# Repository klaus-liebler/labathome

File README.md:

# lab@home

<a target="_blank" href="https://icons8.com/icon/cUjTrEUoGJ2Z/xing">Xing</a> icon by <a target="_blank" href="https://icons8.com">Icons8</a>
<a target="_blank" href="https://icons8.com/icon/3tC9EQumUAuq/github">GitHub</a> icon by <a target="_blank" href="https://icons8.com">Icons8</a>
<a target="_blank" href="https://icons8.com/icon/IuI5Yd3J3qcC/linkedin">LinkedIn</a> icon by <a target="_blank" href="https://icons8.com">Icons8</a>

## Was steckt dahinter?
Das Projekt "lab@home" entstand zu Beginn der Corona-Pandemie. Als Lehrer in einer Hochschule der angewandten Wissenschaften war es dem Initiator ein Anliegen, seinen Studierenden auch 
während des Lockdowns Zugang zu Laborexperimenten in den Bereichen Steuerungstechnik, Regelungstechnik und Informationstechnik zu geben. Leider konnten die Studierenden nicht
mehr in die Hochschullabors, also musste das Labor zu den Studierenden. Nur leider wäre ein Container voll Material pro Student etwas zu aufwändig. Etwas kleineres und vor allem
kostengünstigeres musste her. Und damit waren die grundsätzlichen Anforderungen umrissen und der Initiator machte mich ans Design...

## Was gehört zu lab@home und was kann man damit machen?
Lab@home besteht aus
- einem Hardware-Design
- einer Softwarekomponente
- dieser Dokumentation
- der Beschreibung von Laborexperimenten (nicht veröffentlicht, auf Anfrage stelle ich das gerne zur Verfügung)

Der Entwickler bezeichne lab@home als eine Lehr- und Lernplattform für den Einsatz in Bildungseinrichtungen in den Disziplinen Steuerungstechnik, Regelungstechnik und Informationstechnik.
Ein besonderer Fokus liegt dabei auf der Gebäudeautomation

## Was sind die einzigartigen Merkmale von lab@home?
Lab@home
- ist quelloffen und soll unter der MIT-Lizenz jedem Nutzen stiften!
- kann komplett über den Browser bedient werden   
- ist preiswert und unproblematisch nachbaubar
- kann vielfältig eingesetzt werden

## Genug des Blabla - bitte technisch konkret!
Die Hardware von lab@home ist auf einer 10x10cm großen Platine aufgebaut und enthält die folgenden Komponenten:
- Dual-Prozessor-Konzept
    - Applikation: ESP32-S3 (8M Flash, 2,5MB RAM, Wifi, Bluetooth)
    - I/O & Realtime: STM32G431 (128k Flash, 32k RAM)
- Speichererweiteung über microSD-Slot
- Kommunikation
  - Interne Busse: I2c & 1Wire
  - Extern: Wifi, Bluetooth, RS485 (z.B. für Modbus), CAN (z.B. für CANopen oder OBD2)
  - Optional durch Steckmodule: Ethernet (W5500), GSM (SIM7080G), LoRaWan (RFM95), 2,4GHz (NRF24L01)
- Benutzerinteraktion
  - Taster, Inkrementalencoder
  - IPS-Display 240x240 Pixel, 1,3Zoll (ST7789)
  - Vier RGB-LED (WS2812)
  - Lautsprecher, Mikrofon, Klinkenbuchsen für Aux-In, Line-Out, Kopfhörer (NAU88C22)
- Sensorik
  - Lufttemperatur, Temperatur des Heizwiderstandes (2x DS18B20)
  - Luftfeuchtigkeit (SHT20)
  - Umgebungshelligkeit (LDR)
  - Ausrichtungs und Beschleunigungssensor (LSM6DS3)
  - PIR-Bewegungsmelder
  - Drei universelle ADC-Eingänge, davon einer mit Spannungsteiler
  - Spannungs- und Strommessung
  - Eingänge für Hall-Encoder
  - Optional durch Steckmodule: CO2, Luftqualität, Distanzsensor, Farbsensor
- Aktorik
  - Heizwiderstand, Lüfter, weiße Power-LEDs (alle PWM-Ansteuerung)
  - Zwei universelle DAC-Ausgänge, davon einer mit 0-10V
  - Dreiphasiger Motortreiber (Brushless) (DRV8313)
  - Drei Schrittmotor-Treiber (TMC2209)
  - Anschlüsse für vier (optional sechs) Servos
- Stromversorgung
  - USB
  - USB PD oder PPS (max 20V, 5A, umgesetzt über das UCPD-Peripherial im STM32G431)
  - Hohlstecker 5,5mm
  - MC-Klemmen
  - 18650-Akku
  - Involviert in die Stromversorgung sind 
    - IP5306: Akkuladung, Boot-Converter auf 5V
    - TPS54202: Synchroner Abwärtswandler 8...24V -> 5V
    - TPS2116: Umschaltung zwischen Spannungsquellen
    - AMS1117: LDO 5V->3,3V

Die Software von lab@home besteht aus der eigentlichen Firmware und einer Webapplikation. Viele Experimente können über die Webapplikation gesteuert werden.
Nach dem ersten Start öffnet lab@home einen WIFI-Accesspoint, über den die Webapplikation erreichbar ist und labathome auch in ein bestehendes WIFI-Netzwerk eingebunden werden kann. Dank der Webapplikation benötigt der Anwender keine lokale Software und die Nutzung ist unabhängig vom Betriebssystem möglich (viele meiner Studierenden verwenden Apple-Rechner oder haben nur Chromebooks oder Android-Tablets). Die Webapplikation hat diese Features:
- Programmierung von lab@home mit Funktionsblöcken in Anlehnung an IEC61131 und VDI3814
  - darauf ist der Entwickler besonders stolz!!
  - Speichern und Laden von Programmen möglich
  - Es ist möglich, eine Startapplikation festzulegen, die lab@home automatisch beim Einschalten lädt und ausführt
  - Integrierter Debugger
  - Integrierter Simulator
  - Technisches Detail: Das Funktionsblock-Diagramm wird von einem Java-Script-Compiler im Browser zu einem Binärcode compiliert und "online" zum Mikrocontroller gesendet. Dieser bringt dann das Programm unmittelbar zur Ausführung
- Oberfläche für das Experiment "Identikation einer Regelstrecke mit dem Sprungantwort-Versuch"
- Oberfläche für das Experiment "Parametriertung eines PID-Reglers mit der Einstellregeln nach Chien, Hrones und Reswick"
- Konfigurationsoberfläche für Wifi
- Konfigurationsoberfläche für diverse Systemeinstellungen (in Arbeit)
- Online-Aktualisierung der kompletten Systemsoftware (in Arbeit)

# Getting Started - Hardware
Die aktuellen Schaltpläne und Layouts im KiCad-Format befinden sich im Verzeichnis labathome_pcb

# Getting Started - Software

Die Software muss individuell für jedes Board compiliert werden, weil während des von Gulp gesteuerten Gesamt-Build-Prozesses diverse individuelle Dateien erzeugt und eincompiliert werden. Dazu gehören:
- LabAtHome meldet sich per Sprachausgabe betriebsbereit. Die Ausgabe enthält auch den Hostnamen der Platine, der sich wiederum aus der MAC-Adresse ableitet. Alle Sprachausgaben werden zum Build-Zeitpunkt über Google TTS erzeugt und in Form von MP3-Dateien im Flash abgelegt. Ach ja, LabAtHome kann natürlich MP3 wiedergeben!
- LabAtHome kommuniziert natürlich verschlüsselt! Dazu wird ein privater Schlüssel und ein Zertifikat für eben den Hostnamen erzeugt

## Voraussetzungen
- Installiere Visual Studio Code
    - Installiere und konfiguriere die ESP-IDF Extension
    - Optional: Isntalliere die Extension "Serial Monitor"
- Installiere Node.js
- Installiere Python
- Installiere den Flatbuffers-Compiler (aka. runterladen https://github.com/google/flatbuffers/releases und ausführbare Datei in den "PATH" aufnehmen)
- Checke diverse Repositories aus (Ich gehe davon aus, dass alle Checkouts in c:/repos erfolgen. Einige Pfade sind in den Konfigurationsdateien absolut und auf diesen Pfad angepasst)
    - https://github.com/klaus-liebler/labathome
    - https://github.com/klaus-liebler/espidf-components
    - https://github.com/klaus-liebler/npm-packages
    - https://github.com/klaus-liebler/espidf-component-webmanager,
    - https://github.com/klaus-liebler/esp-idf-components-lcd
- Rufe npm i in den folgenden Verzeichnissen auf:
    - .../labathome/builder
    - .../npm-package/<diverse...>
- Editiere die Datei .../labathome/builder/gulpfile.ts im oberen Bereich direkt nach den Exports. Die Kommentare dort helfen hoffentlich beim Verständnis.
- Lab@Home nutzt die Google TTS Engine während des Build-Prozesses, um individuelle Sprachausgaben zu erzeugen. Der Computer, auf dem der Build durchgeführt wird, muss für den zugriff auf die Google Cloud TTS freigegeben sein: https://cloud.google.com/nodejs/docs/reference/text-to-speech/latest
- Öffne in VS Code eine ESP IDF Console und wechsele in das Verzeichnis .../labathome/builder
- Rufe npm run doOnce auf. Dies erzeugt u.a. ein selbst signiertes Zertifikat , das auf allen Computern als Stammzertifikat installiert werden kann und später zum Signieren der Board-Zertifikate verwendet wird.
- Rufe "npm update" in C:\repos\labathome\espidf-component-labathome\espidf-component-webmanager, auf
- Rufe "npm update" in "C:\repos\labathome\espidf-component-labathome\builder" auf
- Rume "npm run gulp" in "C:\repos\labathome\espidf-component-labathome\builder" auf. Dieses erstellt individuelle Board-Files und die gesamte Web-Anwendung
- TBC

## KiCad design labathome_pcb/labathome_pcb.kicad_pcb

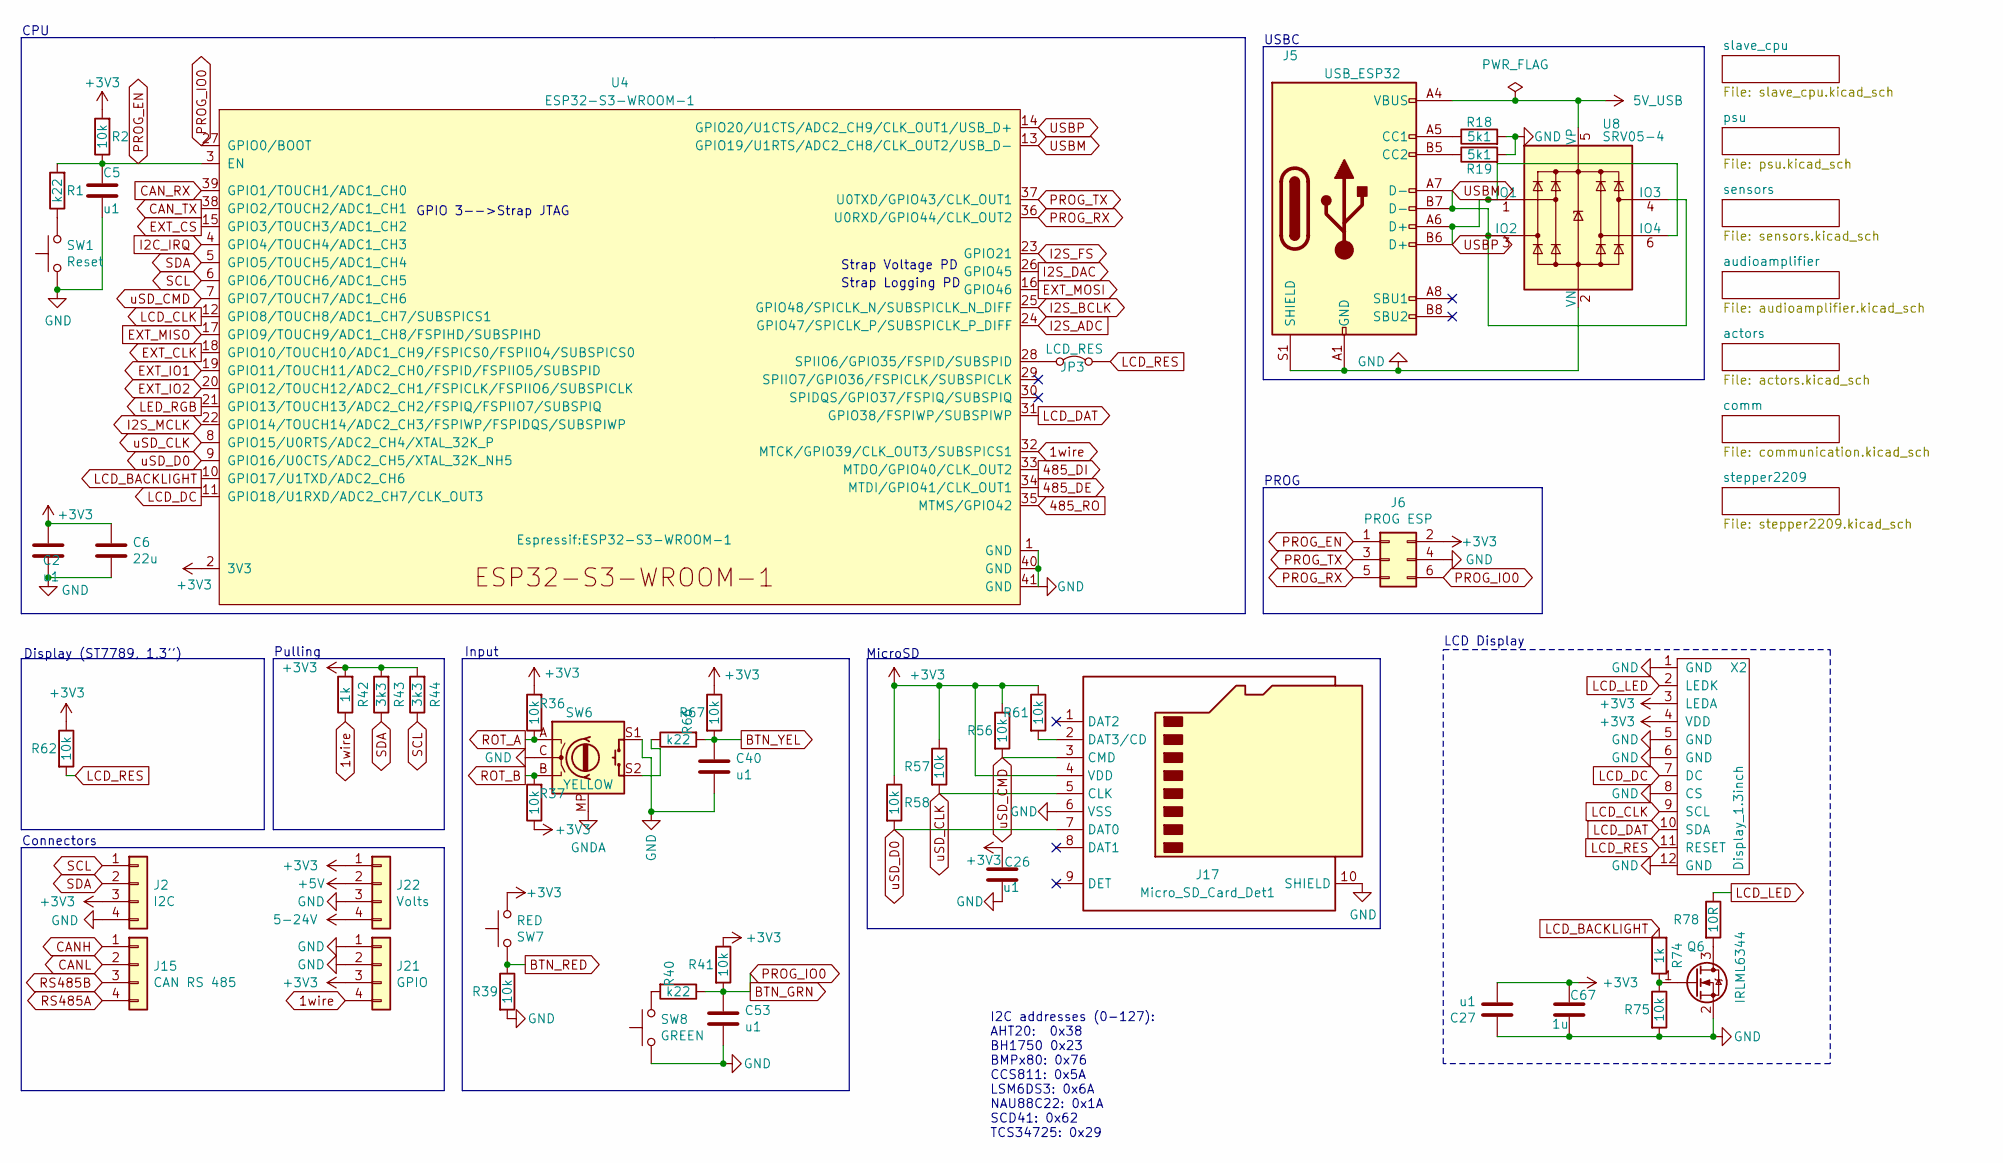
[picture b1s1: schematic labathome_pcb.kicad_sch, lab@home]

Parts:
C2, C5, C26, C27, C40, C53: u1; C_0201_0603Metric; MPN GRM033R61A104KE15D
C6: 22u; C_0603_1608Metric; MPN CL10A226MP8NUNE
C67: 1u; C_0402_1005Metric; MPN CL05A105KA5NQNC
J2: I2C; PhoenixContact_MC_1,5_4-G-3.5_1x04_P3.50mm_Horizontal_small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; MPN KF2EDGR-3.5-4P
J5: USB_ESP32; USB_C_Receptacle_HRO_TYPE-C-31-M-12_smaller; MPN TYPE-C-31-M-12
J6: PROG ESP; IDC_2x03_P1.27mm_Vertical
J15: CAN RS 485; PhoenixContact_MC_1,5_4-G-3.5_1x04_P3.50mm_Horizontal_small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; MPN KF2EDGR-3.5-4P
J17: Micro_SD_Card_Det1; microSD push; MPN TF PUSH
J21: GPIO; PhoenixContact_MC_1,5_4-G-3.5_1x04_P3.50mm_Horizontal_small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; MPN KF2EDGR-3.5-4P
J22: Volts; PhoenixContact_MC_1,5_4-G-3.5_1x04_P3.50mm_Horizontal_small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; MPN KF2EDGR-3.5-4P
JP3: LCD_RES; SolderJumper-2_P1.3mm_Bridged2Bar_RoundedPad1.0x1.5mm
Q6: IRLML6344; SOT-23; MPN AO3400
R1, R40, R66: k22; R_0402_1005Metric; MPN 0402WGF2200TCE
R2, R36, R37, R39, R41, R56, R57, R58, R61, R62, R67, R75: 10k; R_0201_0603Metric; MPN 0201WMF1002TEE
R18, R19: 5k1; R_0201_0603Metric; MPN RC0201FR-075K1L
R42, R74: 1k; R_0402_1005Metric; MPN 0402WGF1001TCE
R43, R44: 3k3; R_0402_1005Metric; MPN 0402WGF3301TCE
R78: 10R; R_1206_3216Metric; MPN 1206W4F100JT5E
SW1: Reset; Button_2x4x3,5_handsolder; MPN TS24CA 250gf 013
SW6: YELLOW; RotaryEncoder_EC11_SMD_handsolder; MPN EC11E0940501
SW7: RED; SW_Push_1P1T_NO_6x6mm_H6.5mm_Reverse; MPN TS-1095E-A6B3-D2
SW8: GREEN; SW_Push_1P1T_NO_6x6mm_H6.5mm_Reverse; MPN TS-1095E-A6B3-D2
U4: ESP32-S3-WROOM-1; MPN ESP32-S3-WROOM-1-N8R2
U8: SRV05-4; SOT-23-6; MPN SRV05-4
X2: Display_1.3inch; IPS_130

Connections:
1wire: J21.4, R42.1, U4.32 (MTCK/GPIO39/CLK_OUT3/SUBSPICS1); also elsewhere on the board
5-24V: J22.4; also elsewhere on the board
5V_USB: J5.A4 (VBUS), J5.A9 (VBUS), J5.B4 (VBUS), J5.B9 (VBUS), U8.5 (VP); also elsewhere on the board
485_DE: U4.34 (MTDI/GPIO41/CLK_OUT1); also elsewhere on the board
485_DI: U4.33 (MTDO/GPIO40/CLK_OUT2); also elsewhere on the board
485_RO: U4.35 (MTMS/GPIO42); also elsewhere on the board
+3V3: C2.1, C6.1, C26.2, C27.2, C67.1, J2.3, J6.2, J17.4 (VDD), J21.3, J22.1, R2.2, R36.2, R37.1, R41.1, R42.2, R43.2, R44.2, R56.1, R57.1, R58.1, R61.1, R62.1, R67.1, SW7.1, U4.2 (3V3), X2.3 (LEDA), X2.4 (VDD); also elsewhere on the board
+5V: J22.2; also elsewhere on the board
BTN_GRN: C53.2, J6.6, R40.1, R41.2, U4.27 (GPIO0/BOOT)
BTN_RED: R39.1, SW7.2; also elsewhere on the board
BTN_YEL: C40.2, R66.2, R67.2; also elsewhere on the board
CANH: J15.1; also elsewhere on the board
CANL: J15.2; also elsewhere on the board
CAN_RX: U4.39 (GPIO1/TOUCH1/ADC1_CH0); also elsewhere on the board
CAN_TX: U4.38 (GPIO2/TOUCH2/ADC1_CH1); also elsewhere on the board
EXT_CLK: U4.18 (GPIO10/TOUCH10/ADC1_CH9/FSPICS0/FSPIIO4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); also elsewhere on the board
EXT_CS: U4.15 (GPIO3/TOUCH3/ADC1_CH2); also elsewhere on the board
EXT_IO1: U4.19 (GPIO11/TOUCH11/ADC2_CH0/FSPID/FSPIIO5/S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); also elsewhere on the board
EXT_IO2: U4.20 (GPIO12/TOUCH12/ADC2_CH1/FSPICLK/FSPIIO6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); also elsewhere on the board
EXT_MISO: U4.17 (GPIO9/TOUCH9/ADC1_CH8/FSPIHD/SUBSPIHD); also elsewhere on the board
EXT_MOSI: U4.16 (GPIO46); also elsewhere on the board
GND: C2.2, C5.2, C6.2, C26.1, C27.1, C40.1, C53.1, C67.2, J2.4, J5.A1 (GND), J5.A12 (GND), J5.B1 (GND), J5.B12 (GND), J5.S1 (SHIELD), J6.4, J17.6 (VSS), J17.10 (SHIELD), J21.1, J21.2, J22.3, Q6.2 (S), R18.2, R19.2, R39.2, R75.2, SW1.1, SW6.C, SW6.S1, SW8.1, U4.1 (GND), U4.40 (GND), U4.41 (GND), U8.2 (VN), X2.1 (GND), X2.5 (GND), X2.6 (GND), X2.8 (CS), X2.12 (GND); also elsewhere on the board
GNDA: SW6.MP; also elsewhere on the board
I2C_IRQ: U4.4 (GPIO4/TOUCH4/ADC1_CH3); also elsewhere on the board
I2S_ADC: U4.24 (GPIO47/SPICLK_P/SUBSPICLK_P_DIFF); also elsewhere on the board
I2S_BCLK: U4.25 (GPIO48/SPICLK_N/SUBSPICLK_N_DIFF); also elsewhere on the board
I2S_DAC: U4.26 (GPIO45); also elsewhere on the board
I2S_FS: U4.23 (GPIO21); also elsewhere on the board
I2S_MCLK: U4.22 (GPIO14/TOUCH14/ADC2_CH3/FSPIWP/FSPIDQS/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); also elsewhere on the board
LCD_BACKLIGHT: R74.2, U4.10 (GPIO17/U1TXD/ADC2_CH6)
LCD_CLK: U4.12 (GPIO8/TOUCH8/ADC1_CH7/SUBSPICS1), X2.9 (SCL)
LCD_DAT: U4.31 (GPIO38/FSPIWP/SUBSPIWP), X2.10 (SDA)
LCD_DC: U4.11 (GPIO18/U1RXD/ADC2_CH7/CLK_OUT3), X2.7 (DC)
LCD_LED: R78.1, X2.2 (LEDK)
LCD_RES: JP3.2 (B), R62.2, X2.11 (RESET); also elsewhere on the board
LED_RGB: U4.21 (GPIO13/TOUCH13/ADC2_CH2/FSPIQ/FSPIIO7/S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); also elsewhere on the board
unnamed: J5.A5 (CC1), R18.1
unnamed: J5.B5 (CC2), R19.1
unnamed: J17.2 (DAT3/CD), R61.2
unnamed: JP3.1 (A), U4.28 (SPIIO6/GPIO35/FSPID/SUBSPID)
unnamed: Q6.3 (D), R78.2
unnamed: Q6.1 (G), R74.1, R75.1
unnamed: R1.1, SW1.2
unnamed: R40.2, SW8.2
unnamed: R66.1, SW6.S2
PROG_EN: C5.1, J6.1, R1.2, R2.1, U4.3 (EN)
PROG_RX: J6.5, U4.36 (U0RXD/GPIO44/CLK_OUT2)
PROG_TX: J6.3, U4.37 (U0TXD/GPIO43/CLK_OUT1)
ROT_A: R36.1, SW6.A; also elsewhere on the board
ROT_B: R37.2, SW6.B; also elsewhere on the board
RS485A: J15.4; also elsewhere on the board
RS485B: J15.3; also elsewhere on the board
SCL: J2.1, R44.1, U4.6 (GPIO6/TOUCH6/ADC1_CH5); also elsewhere on the board
SDA: J2.2, R43.1, U4.5 (GPIO5/TOUCH5/ADC1_CH4); also elsewhere on the board
USBM: J5.A7 (D-), J5.B7 (D-), U4.13 (GPIO19/U1RTS/ADC2_CH8/CLK_OUT2/USB_D-), U8.3 (IO2), U8.4 (IO3)
USBP: J5.A6 (D+), J5.B6 (D+), U4.14 (GPIO20/U1CTS/ADC2_CH9/CLK_OUT1/USB_D+), U8.1 (IO1), U8.6 (IO4)
uSD_CLK: J17.5 (CLK), R57.2, U4.8 (GPIO15/U0RTS/ADC2_CH4/XTAL_32K_P)
uSD_CMD: J17.3 (CMD), R56.2, U4.7 (GPIO7/TOUCH7/ADC1_CH6)
uSD_D0: J17.7 (DAT0), R58.2, U4.9 (GPIO16/U0CTS/ADC2_CH5/XTAL_32K_NH5)

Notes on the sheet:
USBC
Connectors
I2C addresses (0-127): AHT20: 0x38 BH1750 0x23 BMPx80: 0x76 CCS811: 0x5A LSM6DS3: 0x6A NAU88C22: 0x1A SCD41: 0x62 TCS34725: 0x29
Pulling
GPIO 3-->Strap JTAG
Strap Logging PD
Input
Strap Voltage PD
MicroSD
CPU
PROG
Display (ST7789, 1,3'')
LCD Display

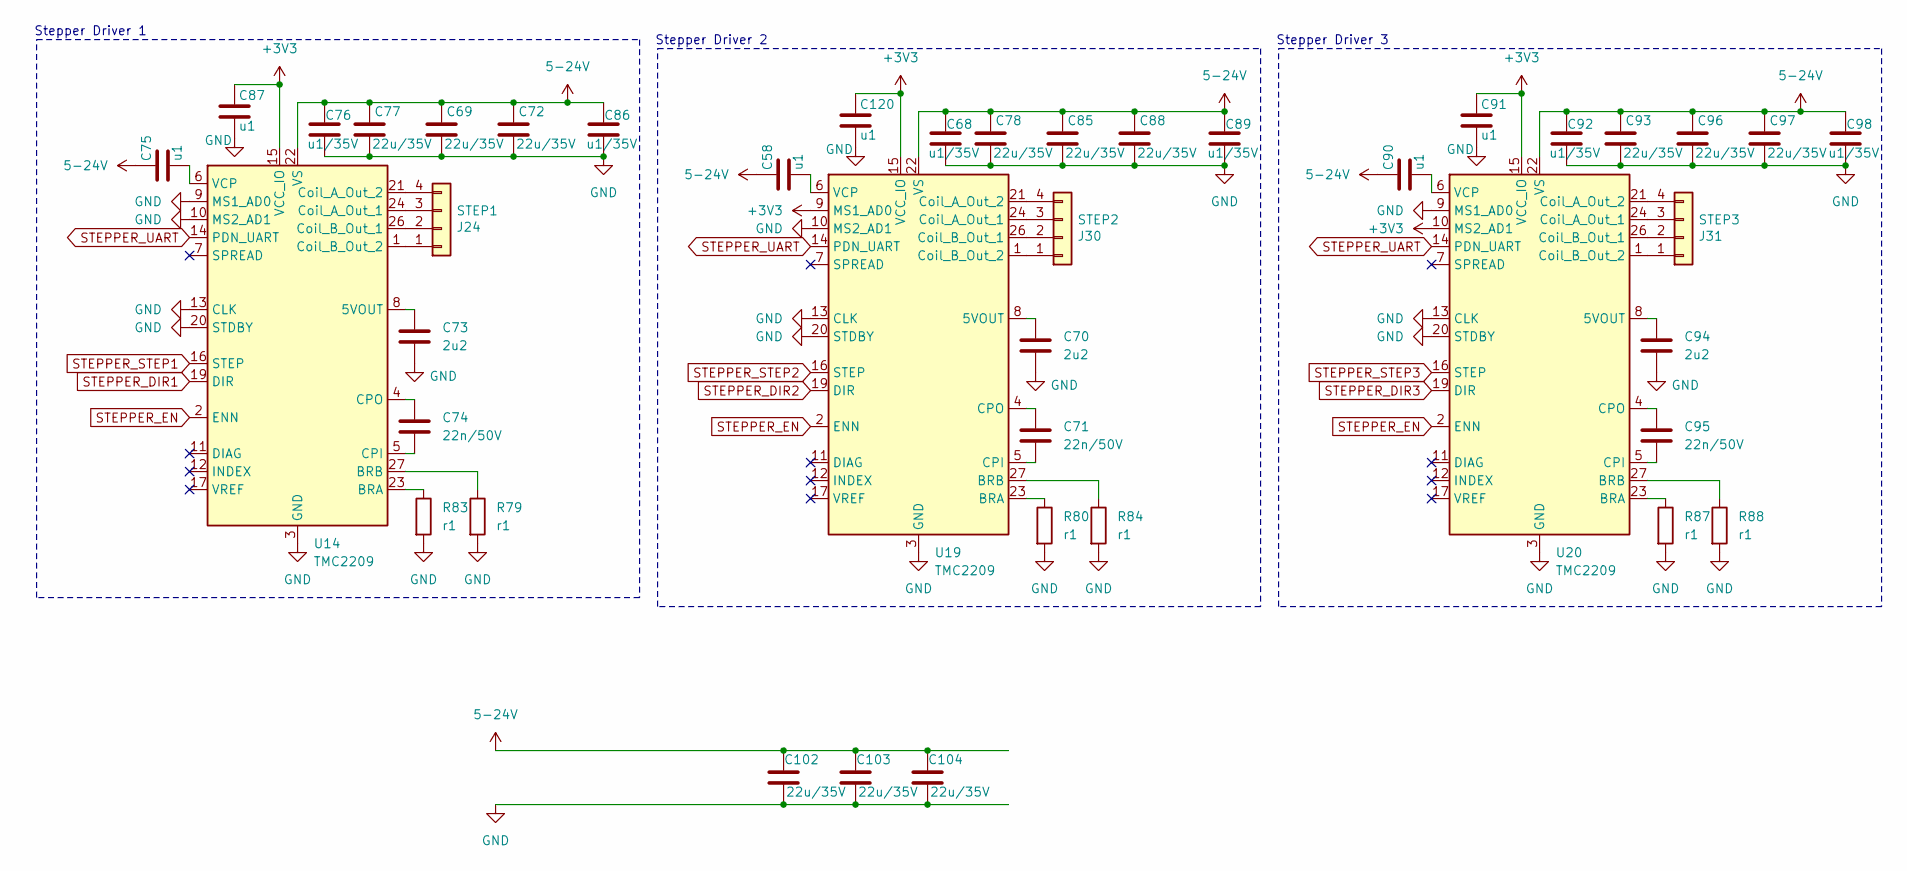
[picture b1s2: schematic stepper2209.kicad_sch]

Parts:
C58, C75, C87, C90, C91, C120: u1; C_0201_0603Metric; MPN GRM033R61A104KE15D
C68, C76, C86, C89, C92, C98: u1/35V; C_0603_1608Metric; MPN CC0603KRX7R9BB104
C69, C72, C77, C78, C85, C88, C93, C96, C97, C102, C103, C104: 22u/35V; C_0805_2012Metric; MPN CGA0805X5R226M350MT
C70, C73, C94: 2u2; C_0402_1005Metric; MPN CL05A225MQ5NSNC
C71, C74, C95: 22n/50V; C_0402_1005Metric; MPN GRM155R71H223KA12D
J24: STEP1; JST_XH_S4B-XH-A-1_1x04_P2.50mm_Horizontal_SmallerCourtyard; MPN XH-4AW
J30: STEP2; JST_XH_S4B-XH-A-1_1x04_P2.50mm_Horizontal_SmallerCourtyard; MPN XH-4AW
J31: STEP3; JST_XH_S4B-XH-A-1_1x04_P2.50mm_Horizontal_SmallerCourtyard; MPN XH-4AW
R79, R80, R83, R84, R87, R88: r1; R_1206_3216Metric; MPN FRM121WFR100TM
U14, U19, U20: TMC2209; QFN-28-1EP_5x5mm_P0.5mm_EP3.75x3.75mm_ThermalVias; MPN TMC2209-LA-T

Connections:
5-24V: C58.1, C68.1, C69.2, C72.2, C75.1, C76.1, C77.2, C78.2, C85.2, C86.1, C88.2, C89.1, C90.1, C92.1, C93.2, C96.2, C97.2, C98.1, C102.2, C103.2, C104.2, U14.22 (VS), U14.28 (VS), U19.22 (VS), U19.28 (VS), U20.22 (VS), U20.28 (VS); also elsewhere on the board
+3V3: C87.1, C91.1, C120.1, U14.15 (VCC_IO), U19.9 (MS1_AD0), U19.15 (VCC_IO), U20.10 (MS2_AD1), U20.15 (VCC_IO); also elsewhere on the board
FAN_DRIVE: U20.19 (DIR); also elsewhere on the board
GND: C68.2, C69.1, C70.2, C72.1, C73.2, C76.2, C77.1, C78.1, C85.1, C86.2, C87.2, C88.1, C89.2, C91.2, C92.2, C93.1, C94.2, C96.1, C97.1, C98.2, C102.1, C103.1, C104.1, C120.2, R79.2, R80.2, R83.2, R84.2, R87.2, R88.2, U14.3 (GND), U14.9 (MS1_AD0), U14.10 (MS2_AD1), U14.13 (CLK), U14.18 (GND), U14.20 (STDBY), U14.25 (GND), U14.29 (PAD), U19.3 (GND), U19.10 (MS2_AD1), U19.13 (CLK), U19.18 (GND), U19.20 (STDBY), U19.25 (GND), U19.29 (PAD), U20.3 (GND), U20.9 (MS1_AD0), U20.13 (CLK), U20.18 (GND), U20.20 (STDBY), U20.25 (GND), U20.29 (PAD); also elsewhere on the board
LED_WHITE_P: U19.19 (DIR); also elsewhere on the board
unnamed: J24.1, U14.1 (Coil_B_Out_2)
unnamed: J24.2, U14.26 (Coil_B_Out_1)
unnamed: J24.3, U14.24 (Coil_A_Out_1)
unnamed: J24.4, U14.21 (Coil_A_Out_2)
unnamed: J30.1, U19.1 (Coil_B_Out_2)
unnamed: J30.2, U19.26 (Coil_B_Out_1)
unnamed: J30.3, U19.24 (Coil_A_Out_1)
unnamed: J30.4, U19.21 (Coil_A_Out_2)
unnamed: J31.1, U20.1 (Coil_B_Out_2)
unnamed: J31.2, U20.26 (Coil_B_Out_1)
unnamed: J31.3, U20.24 (Coil_A_Out_1)
unnamed: J31.4, U20.21 (Coil_A_Out_2)
unnamed: C73.1, U14.8 (5VOUT)
unnamed: R83.1, U14.23 (BRA)
unnamed: R79.1, U14.27 (BRB)
unnamed: C74.2, U14.5 (CPI)
unnamed: C74.1, U14.4 (CPO)
unnamed: C75.2, U14.6 (VCP)
unnamed: C70.1, U19.8 (5VOUT)
unnamed: R80.1, U19.23 (BRA)
unnamed: R84.1, U19.27 (BRB)
unnamed: C71.2, U19.5 (CPI)
unnamed: C71.1, U19.4 (CPO)
unnamed: C58.2, U19.6 (VCP)
unnamed: C94.1, U20.8 (5VOUT)
unnamed: R87.1, U20.23 (BRA)
unnamed: R88.1, U20.27 (BRB)
unnamed: C95.2, U20.5 (CPI)
unnamed: C95.1, U20.4 (CPO)
unnamed: C90.2, U20.6 (VCP)
STEPPER_DIR1: U14.19 (DIR); also elsewhere on the board
STEPPER_EN: U14.2 (ENN), U19.2 (ENN), U20.2 (ENN); also elsewhere on the board
STEPPER_STEP1: U14.16 (STEP); also elsewhere on the board
STEPPER_STEP2: U19.16 (STEP); also elsewhere on the board
STEPPER_STEP3: U20.16 (STEP); also elsewhere on the board
STEPPER_UART: U14.14 (PDN_UART), U19.14 (PDN_UART), U20.14 (PDN_UART); also elsewhere on the board

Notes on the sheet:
Stepper Driver 3
Stepper Driver 1
Stepper Driver 2

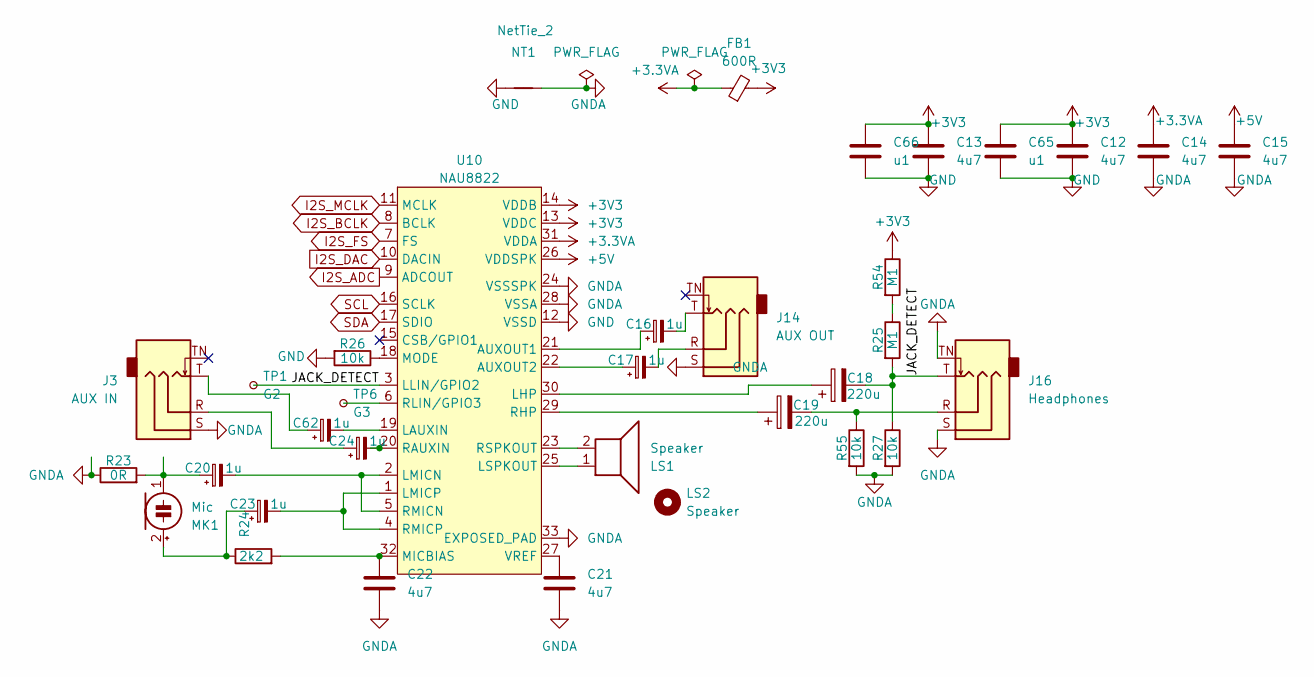
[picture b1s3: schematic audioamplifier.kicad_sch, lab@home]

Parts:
C12, C13, C14, C15, C21, C22: 4u7; C_0402_1005Metric; MPN CL05A475MP5NRNC
C16, C17, C20, C23, C24, C62: 1u; CP_EIA-3216-10_Kemet-I; MPN TAJA105K016RNJ
C18, C19: 220u; CP_Elec_6.3x5.4; MPN RVE0J221M0605
C65, C66: u1; C_0201_0603Metric; MPN GRM033R61A104KE15D
FB1: 600R; L_0603_1608Metric; MPN BLM18AG601SN1D
J3: AUX IN; PJ-327A; MPN PJ-327A0-SMT
J14: AUX OUT; PJ-327A; MPN PJ-327A0-SMT
J16: Headphones; PJ-327A; MPN PJ-327A0-SMT
LS1: Speaker; L_Abracon_ASPI-0425
LS2: Speaker; SPEAKER_2415
MK1: Mic; Microphone_6mm; MPN GMI6050P-64DB
NT1: NetTie_2; NetTie-2_SMD_Pad0.5mm
R23: 0R; R_0805_2012Metric_Pad1.20x1.40mm_HandSolder; MPN 0805W8F0000T5E
R24: 2k2; R_0402_1005Metric; MPN 0402WGF2201TCE
R25, R54: M1; R_0201_0603Metric; MPN 0201WMF1003TEE
R26, R27, R55: 10k; R_0201_0603Metric; MPN 0201WMF1002TEE
TP1: G2; TestPoint_THTPad_D1.0mm_Drill0.5mm
TP6: G3; TestPoint_THTPad_D1.0mm_Drill0.5mm
U10: NAU8822; QFN-32-1EP_5x5mm_P0.5mm_EP3.6x3.6mm_ThermalVias; MPN NAU88C22YG

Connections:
+3.3VA: C14.1, FB1.1, U10.31 (VDDA)
+3V3: C12.1, C13.1, C65.1, C66.1, FB1.2, R54.1, U10.13 (VDDC), U10.14 (VDDB); also elsewhere on the board
+5V: C15.1, U10.26 (VDDSPK); also elsewhere on the board
/audioamplifier/JACK_DETECT: C18.2, J16.T, R25.2, R27.1, TP1.1, U10.3 (LLIN/GPIO2)
GND: C12.2, C13.2, C65.2, C66.2, NT1.1, R26.2, U10.12 (VSSD); also elsewhere on the board
GNDA: C14.2, C15.2, C21.2, C22.2, J3.S, J14.S, J16.S, J16.TN, NT1.2, R23.1, R27.2, R55.2, U10.24 (VSSSPK), U10.28 (VSSA), U10.33 (EXPOSED_PAD); also elsewhere on the board
I2S_ADC: U10.9 (ADCOUT); also elsewhere on the board
I2S_BCLK: U10.8 (BCLK); also elsewhere on the board
I2S_DAC: U10.10 (DACIN); also elsewhere on the board
I2S_FS: U10.7 (FS); also elsewhere on the board
I2S_MCLK: U10.11 (MCLK); also elsewhere on the board
unnamed: C16.2, J14.T
unnamed: C17.2, J14.R
unnamed: C19.2, J16.R, R55.1
unnamed: C24.1, J3.R
unnamed: C62.1, J3.T
unnamed: C23.1, MK1.2 (+), R24.1
unnamed: C20.1, MK1.1 (-), R23.2
unnamed: R25.1, R54.2
unnamed: C16.1, U10.21 (AUXOUT1)
unnamed: C17.1, U10.22 (AUXOUT2)
unnamed: C62.2, U10.19 (LAUXIN)
unnamed: C18.1, U10.30 (LHP)
unnamed: C20.2, U10.2 (LMICN), U10.5 (RMICN)
unnamed: C23.2, U10.1 (LMICP), U10.4 (RMICP)
unnamed: LS1.1, U10.25 (LSPKOUT)
unnamed: C22.1, R24.2, U10.32 (MICBIAS)
unnamed: R26.1, U10.18 (MODE)
unnamed: C24.2, U10.20 (RAUXIN)
unnamed: C19.1, U10.29 (RHP)
unnamed: TP6.1, U10.6 (RLIN/GPIO3)
unnamed: LS1.2, U10.23 (RSPKOUT)
unnamed: C21.1, U10.27 (VREF)
SCL: U10.16 (SCLK); also elsewhere on the board
SDA: U10.17 (SDIO); also elsewhere on the board

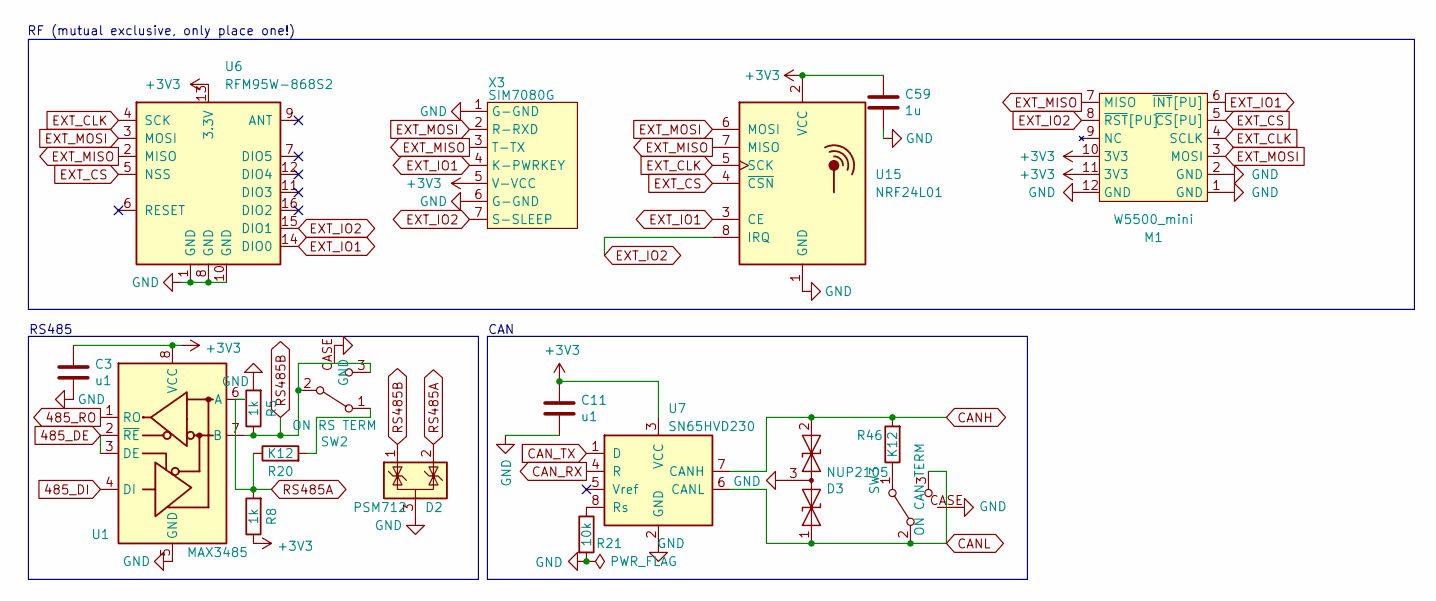
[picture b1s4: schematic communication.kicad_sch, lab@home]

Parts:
C3, C11: u1; C_0201_0603Metric; MPN GRM033R61A104KE15D
C59: 1u; C_0402_1005Metric; MPN CL05A105KA5NQNC
D2: PSM712; SOT-23_Handsoldering; MPN PSM712
D3: NUP2105; SOT-23_Handsoldering; MPN NUP2105L
M1: W5500_mini; W5500-mini
R5, R8: 1k; R_0402_1005Metric; MPN 0402WGF1001TCE
R20, R46: K12; R_1206_3216Metric_Pad1.30x1.75mm_HandSolder; MPN 1206W4F1200T5E
R21: 10k; R_0201_0603Metric; MPN 0201WMF1002TEE
SW2: ON RS TERM; SW_SPDT_PCM12_handsolder; MPN MSK12C02
SW3: ON CAN TERM; SW_SPDT_PCM12_handsolder; MPN MSK12C02
U1: MAX3485; SOIC-8_3.9x4.9mm_Pitch1.27mm_handsolder; MPN SP3485EEN(UMW)
U6: RFM95W-868S2; HOPERF_RFM9XW_THT
U7: SN65HVD230; SOIC-8_3.9x4.9mm_Pitch1.27mm_handsolder; MPN SN65HVD230DR
U15: NRF24L01; nRF24L01_Breakout
X3: SIM7080G; SIM7080G_AND_MODULE

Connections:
485_DE: U1.2 (~RE), U1.3 (DE); also elsewhere on the board
485_DI: U1.4 (DI); also elsewhere on the board
485_RO: U1.1 (RO); also elsewhere on the board
+3V3: C3.2, C11.1, C59.1, M1.10 (3V3), M1.11 (3V3), R8.1, U1.8 (VCC), U6.13 (3.3V), U7.3 (VCC), U15.2 (VCC), X3.5 (V-VCC); also elsewhere on the board
CANH: D3.2 (A2), R46.2, U7.7 (CANH); also elsewhere on the board
CANL: D3.1 (A1), SW3.2 (B), SW3.3 (C), U7.6 (CANL); also elsewhere on the board
CAN_RX: U7.4 (R); also elsewhere on the board
CAN_TX: U7.1 (D); also elsewhere on the board
EXT_CLK: M1.4 (SCLK), U6.4 (SCK), U15.5 (SCK); also elsewhere on the board
EXT_CS: M1.5 (~CS[PU]), U6.5 (NSS), U15.4 (~CSN); also elsewhere on the board
EXT_IO1: M1.6 (~INT[PU]), U6.14 (DIO0), U15.3 (CE), X3.4 (K-PWRKEY); also elsewhere on the board
EXT_IO2: M1.8 (~RST[PU]), U6.15 (DIO1), U15.8 (IRQ), X3.7 (S-SLEEP); also elsewhere on the board
EXT_MISO: M1.7 (MISO), U6.2 (MISO), U15.7 (MISO), X3.3 (T-TX); also elsewhere on the board
EXT_MOSI: M1.3 (MOSI), U6.3 (MOSI), U15.6 (MOSI), X3.2 (R-RXD); also elsewhere on the board
GND: C3.1, C11.2, C59.2, D2.3 (A), D3.3 (common), M1.1 (GND), M1.2 (GND), M1.12 (GND), R5.2, R21.2, SW2.CASE, SW3.CASE, U1.5 (GND), U6.1 (GND), U6.8 (GND), U6.10 (GND), U7.2 (GND), U15.1 (GND), X3.1 (G-GND), X3.6 (G-GND); also elsewhere on the board
unnamed: R20.2, SW2.1 (A)
unnamed: R46.1, SW3.1 (A)
unnamed: R21.1, U7.8 (Rs)
RS485A: D2.2 (K), R8.2, R20.1, U1.6 (A); also elsewhere on the board
RS485B: D2.1 (K), R5.1, SW2.2 (B), SW2.3 (C), U1.7 (B); also elsewhere on the board

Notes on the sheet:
RF (mutual exclusive, only place one!)
RS485
CAN

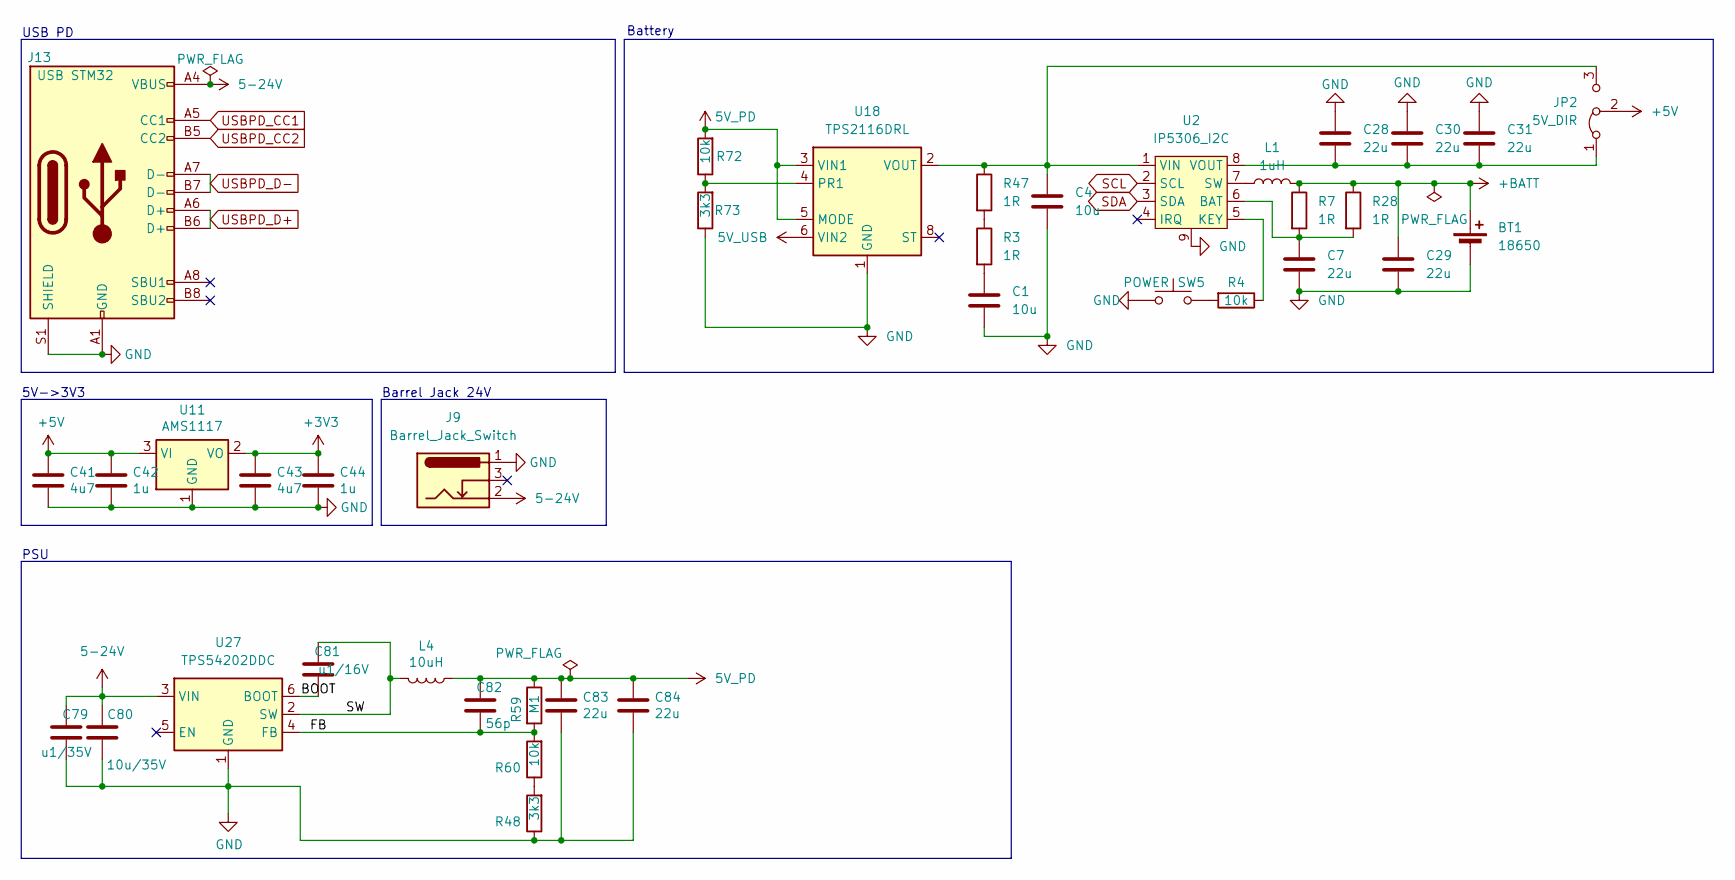
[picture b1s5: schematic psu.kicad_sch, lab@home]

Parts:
BT1: 18650; BatteryHolder_MPD_BH-18650-PC2
C1, C4: 10u; C_0805_2012Metric; MPN CGA0805X5R106K350MT
C7, C28, C29, C30, C31, C83, C84: 22u; C_0603_1608Metric; MPN CL10A226MP8NUNE
C41, C43: 4u7; C_0402_1005Metric; MPN CL05A475MP5NRNC
C42, C44: 1u; C_0402_1005Metric; MPN CL05A105KA5NQNC
C79: u1/35V; C_0603_1608Metric; MPN CC0603KRX7R9BB104
C80: 10u/35V; C_0805_2012Metric; MPN CGA0805X5R106K350MT
C81: u1/16V; C_0603_1608Metric; MPN CC0603KRX7R9BB104
C82: 56p; C_0402_1005Metric; MPN CC0402JRNPO9BN560
J9: Barrel_Jack_Switch; BarrelJack_Horizontal; MPN DC-005 2.0
J13: USB STM32; USB_C_Receptacle_HRO_TYPE-C-31-M-12_smaller; MPN TYPE-C-31-M-12
JP2: 5V_DIR; SolderJumper-3_P1.3mm_Bridged2Bar12_RoundedPad1.0x1.5mm
L1: 1uH; L_0630; MPN FXL0630-1R0-M
L4: 10uH; L_0630; MPN FXL0630-100-M
R3, R7, R28, R47: 1R; R_0603_1608Metric; MPN 0603WAF100KT5E
R4, R60, R72: 10k; R_0201_0603Metric; MPN 0201WMF1002TEE
R48, R73: 3k3; R_0402_1005Metric; MPN 0402WGF3301TCE
R59: M1; R_0201_0603Metric; MPN 0201WMF1003TEE
SW5: POWER; SW_Push_1P1T_NO_6x6mm_H6.5mm_Reverse; MPN TS-1095E-A6B3-D2
U2: IP5306_I2C; HSOP-8-1EP_3.9x4.9mm_P1.27mm_EP2.3x2.3mm_ThermalVias; MPN INJOINIC IP5306-I2C
U11: AMS1117; SOT-223-3_TabPin2; MPN AMS1117-3.3
U18: TPS2116DRL; SOT-583-8; MPN TPS2116DRLR
U27: TPS54202DDC; SOT-23-6_Handsoldering; MPN TPS54202DDCR

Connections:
5-24V: C79.2, C80.2, J9.2, J13.A4 (VBUS), J13.A9 (VBUS), J13.B4 (VBUS), J13.B9 (VBUS), U27.3 (VIN); also elsewhere on the board
5V_PD: C82.2, C83.1, C84.1, L4.1, R59.1, R72.2, U18.3 (VIN1), U18.5 (MODE)
5V_USB: U18.6 (VIN2); also elsewhere on the board
+3V3: C43.2, C44.1, U11.2 (VO); also elsewhere on the board
+5V: C41.2, C42.1, JP2.2 (C), U11.3 (VI); also elsewhere on the board
+BATT: BT1.1 (+), C29.1, L1.2, R7.1, R28.1
/psu/BOOT: C81.1, U27.6 (BOOT)
/psu/FB: C82.1, R59.2, R60.2, U27.4 (FB)
/psu/SW: C81.2, L4.2, U27.2 (SW)
GND: BT1.2 (-), C1.2, C4.2, C7.2, C28.1, C29.2, C30.1, C31.1, C41.1, C42.2, C43.1, C44.2, C79.1, C80.1, C83.2, C84.2, J9.1, J13.A1 (GND), J13.A12 (GND), J13.B1 (GND), J13.B12 (GND), J13.S1 (SHIELD), R48.1, R73.1, SW5.1, U2.9, U11.1 (GND), U18.1 (GND), U27.1 (GND); also elsewhere on the board
unnamed: C1.1, R3.2
unnamed: C28.2, C30.2, C31.2, JP2.1 (A), U2.8 (VOUT)
unnamed: C4.1, JP2.3 (B), R47.1, U2.1 (VIN), U18.2 (VOUT), U18.7 (VOUT)
unnamed: R3.1, R47.2
unnamed: R4.2, SW5.2
unnamed: R48.2, R60.1
unnamed: C7.1, R7.2, R28.2, U2.6 (BAT)
unnamed: R4.1, U2.5 (KEY)
unnamed: L1.1, U2.7 (SW)
unnamed: R72.1, R73.2, U18.4 (PR1)
SCL: U2.2 (SCL); also elsewhere on the board
SDA: U2.3 (SDA); also elsewhere on the board
USBPD_CC1: J13.A5 (CC1); also elsewhere on the board
USBPD_CC2: J13.B5 (CC2); also elsewhere on the board
USBPD_D+: J13.A6 (D+), J13.B6 (D+); also elsewhere on the board
USBPD_D-: J13.A7 (D-), J13.B7 (D-); also elsewhere on the board

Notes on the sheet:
USB PD
Barrel Jack 24V
5V->3V3
Battery
PSU
